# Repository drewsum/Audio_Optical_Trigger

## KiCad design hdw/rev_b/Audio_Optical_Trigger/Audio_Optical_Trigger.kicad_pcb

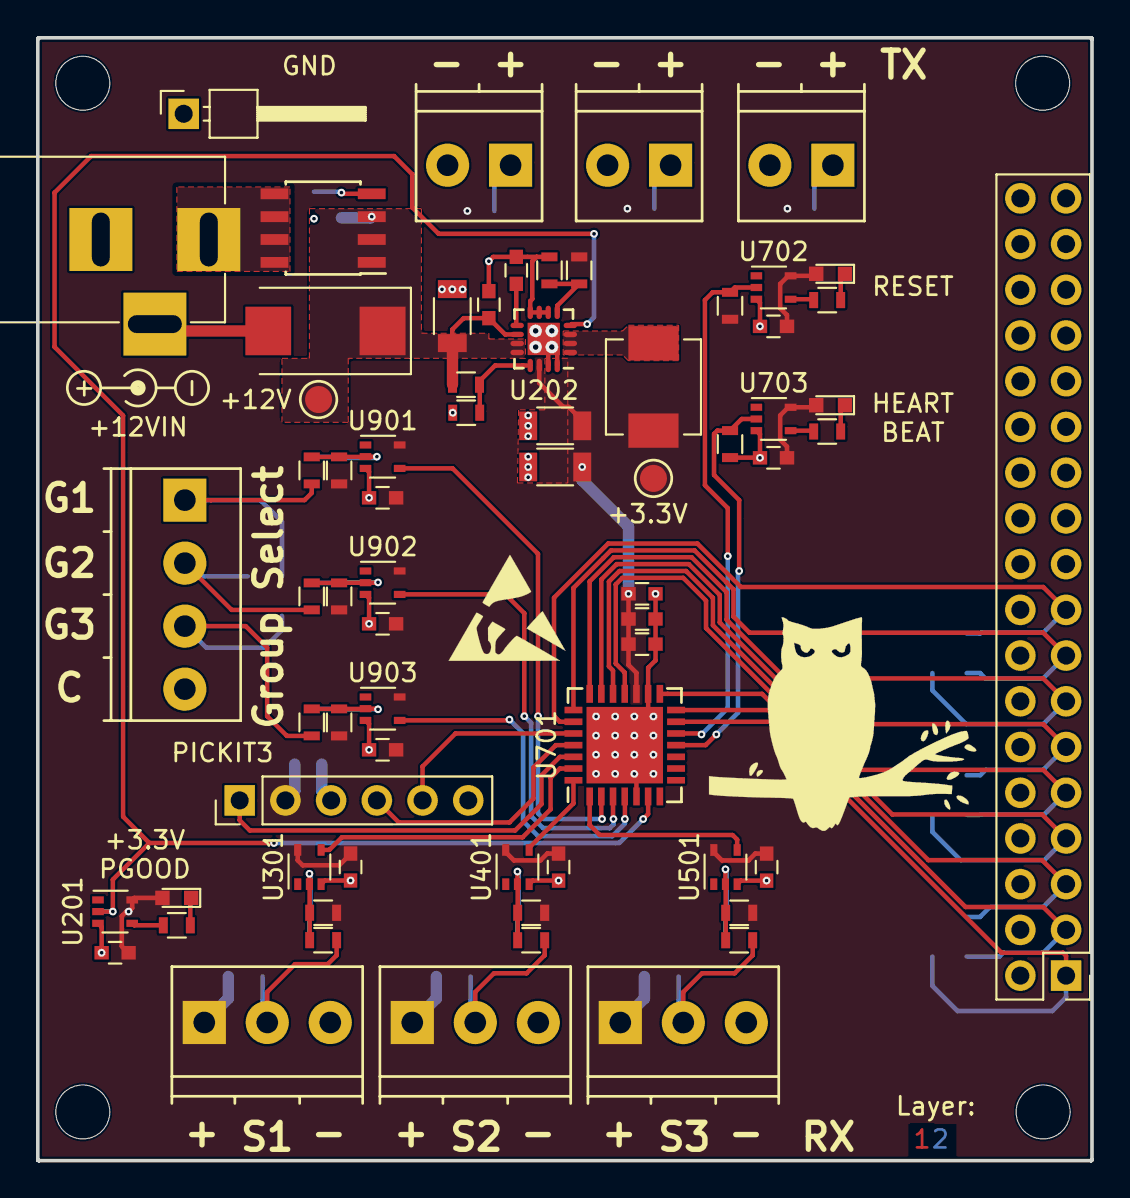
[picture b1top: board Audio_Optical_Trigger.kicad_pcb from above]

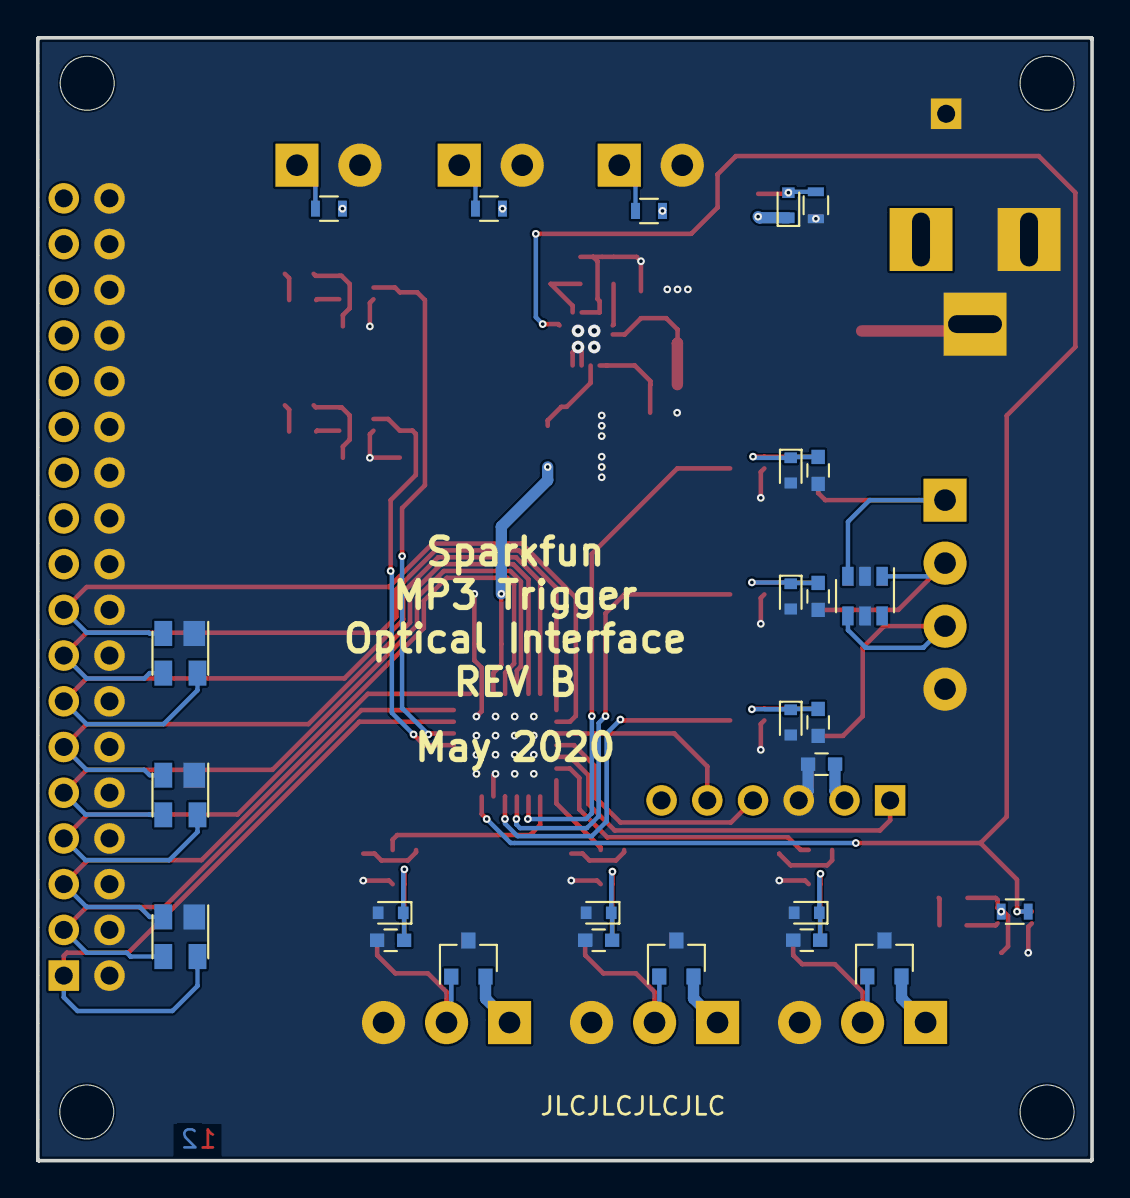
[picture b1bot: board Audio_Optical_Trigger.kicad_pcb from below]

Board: 2 copper layers, 58.6 x 62.4 mm, 98 parts (30 on the bottom side), 51 nets.

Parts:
C201, C205, C302, C402, C502, C601, C701, C704, C705, C904, C905, C906: 0.1uF; C_0603
C202: 100uF; CP_Tantalum_Case-D_EIA-7343-31_Reflow
C203: 10uF; C_1206
C204, C301, C401, C501, C702, C901, C902, C903: 10nF; C_0603
C206, C207: 22uF; C_1206
C703: 1nF; C_0603
D201: MM5Z10V; D_SOD-523
D202, D702: GREEN; LED_0603
D301, D401, D501: CM1213A-01SO; SOT-23
D302, D402, D502, D902, D903, D904: MM5Z3V6; D_SOD-523
D701: RED; LED_0603
D901: ESDA6V1BC6; SOT-23-6
D1001, D1002, D1003: SP0503BAHT; SOT-143
H1101, H1102, H1103, H1104: MountingHole; MountingHole_3mm
J201: +12VIN; BARREL_JACK
J301: TX1; TerminalBlock_Phoenix_PT-3.5mm_2pol
J302: RX1; TerminalBlock_Phoenix_PT-3.5mm_3pol
J401: TX2; TerminalBlock_Phoenix_PT-3.5mm_2pol
J402: RX2; TerminalBlock_Phoenix_PT-3.5mm_3pol
J501: TX3; TerminalBlock_Phoenix_PT-3.5mm_2pol
J502: RX3; TerminalBlock_Phoenix_PT-3.5mm_3pol
J601: PICKIT3; PinHeader_1x06_P2.54mm_Vertical
J901: Group Select; TerminalBlock_Phoenix_PT-3.5mm_4pol
J1001: Trigger Output; Pin_Header_Straight_2x18_Pitch2.54mm
L201: 2.2u; L_Vishay_IHLP-2020
Q201: IRF7404; SOIC-8_3.9x4.9mm_Pitch1.27mm
R201, R203, R303, R403, R503, R701, R702, R904, R905, R906: 10k; R_0603
R202, R207, R703, R704: 2k; R_0603
R204: 100k; R_0603
R205, R206: 10.5k; R_0603
R301, R401, R501: 0; R_0603
R302, R402, R502, R901, R902, R903: 100; R_0603
TP201: TP; Pin_Header_Angled_1x01_Pitch2.54mm
TP202, TP203: TP; Test_Point
U201, U702, U703, U901, U902, U903: 74LVC1G14; SOT-353_SC-70-5
U202: TPS62130; QFN-16-1EP_3x3mm_Pitch0.5mm
U301, U401, U501: 74LVC1G17; SOT-353_SC-70-5
U701: PIC18F27K40T-I_ML; QFN-28-1EP_6x6mm_Pitch0.65mm

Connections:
+3V3: C201.1, C206.1, C207.1, C302.1, C402.1, C502.1, C601.1, C701.1, C702.1, C703.1, C704.1, C705.1, C904.1, C905.1, C906.1, D202.2, D301.2, D401.2, D501.2, D701.2, D702.2, J302.1, J402.1, J502.1, J601.2, L201.2, R203.1, R206.1, R301.1, R303.1, R401.1, R403.1, R501.1, R503.1, R701.1, R904.1, R905.1, R906.1, TP203.1, U201.5, U202.14, U301.5, U401.5, U501.5, U701.17, U702.5, U703.5, U901.5, U902.5, U903.5
+12V: C202.1, C203.1, C205.1, D201.1, Q201.1, Q201.2, Q201.3, R204.1, TP202.1, U202.10, U202.11, U202.12
/Input Channel 1/YELLOW: D301.1, J302.2, R302.2
/Input Channel 2/YELLOW: D401.1, J402.2, R402.2
/Input Channel 3/YELLOW: D501.1, J502.2, R502.2
GND: C201.2, C202.2, C203.2, C204.2, C205.2, C206.2, C207.2, C301.2, C302.2, C401.2, C402.2, C501.2, C502.2, C601.2, C701.2, C702.2, C703.2, C704.2, C705.2, C901.2, C902.2, C903.2, C904.2, C905.2, C906.2, D301.3, D302.2, D401.3, D402.2, D501.3, D502.2, D901.2, D901.5, D902.2, D903.2, D904.2, D1001.1, D1002.1, D1003.1, J201.2, J201.3, J301.2, J302.3, J401.2, J402.3, J501.2, J502.3, J601.3, J901.4, J1001.2, J1001.4, J1001.6, J1001.8, J1001.10, J1001.12, J1001.14, J1001.16, J1001.18, J1001.20, J1001.22, J1001.24, J1001.26, J1001.28, J1001.30, J1001.32, J1001.34, J1001.36, R201.2, R205.2, R207.2, R702.2, TP201.1, U201.3, U202.6, U202.7, U202.8, U202.15, U202.16, U202.17, U301.3, U401.3, U501.3, U701.5, U701.16, U701.29, U702.3, U703.3, U901.3, U902.3, U903.3
Heartbeat_LED: R702.1, U701.11, U703.2
ICSPCLK: J601.5, U701.24
ICSPDAT: J601.4, U701.25
Input_Channel_1: U301.4, U701.27
Input_Channel_2: U401.4, U701.28
Input_Channel_3: U501.4, U701.1
unnamed: C204.1, U202.9
unnamed: C301.1, D302.1, R302.1, R303.2, U301.2
unnamed: C401.1, D402.1, R402.1, R403.2, U401.2
unnamed: C501.1, D502.1, R502.1, R503.2, U501.2
unnamed: C901.1, D902.1, R901.1, R904.2, U901.2
unnamed: C902.1, D903.1, R902.1, R905.2, U902.2
unnamed: C903.1, D904.1, R903.1, R906.2, U903.2
unnamed: D201.2, Q201.4, R201.1
unnamed: D202.1, R202.1
unnamed: D701.1, R703.1
unnamed: D702.1, R704.1
unnamed: D901.1, J901.2, R902.2
unnamed: D901.3, J901.1, R901.2
unnamed: D901.4, J901.3, R903.2
unnamed: J201.1, Q201.5, Q201.6, Q201.7, Q201.8
unnamed: J301.1, R301.2
unnamed: J401.1, R401.2
unnamed: J501.1, R501.2
unnamed: L201.1, U202.1, U202.2, U202.3
unnamed: R202.2, U201.4
unnamed: R204.2, R205.1, U202.13
unnamed: R206.2, R207.1, U202.5
unnamed: R703.2, U702.4
unnamed: R704.2, U703.4
Output_Group_Select_1: U701.2, U901.4
Output_Group_Select_2: U701.3, U902.4
Output_Group_Select_3: U701.4, U903.4
POS3P3_PGOOD: R203.2, U201.2, U202.4, U701.6
Reset_LED: R701.2, U701.12, U702.2
~MCLR: J601.1, U701.26
~Output_Group_1_Channel_1: D1001.4, J1001.1, U701.13
~Output_Group_1_Channel_2: D1001.3, J1001.3, U701.14
~Output_Group_1_Channel_3: D1001.2, J1001.5, U701.15
~Output_Group_2_Channel_1: D1002.4, J1001.7, U701.18
~Output_Group_2_Channel_2: D1002.3, J1001.9, U701.19
~Output_Group_2_Channel_3: D1002.2, J1001.11, U701.20
~Output_Group_3_Channel_1: D1003.4, J1001.13, U701.21
~Output_Group_3_Channel_2: D1003.3, J1001.15, U701.22
~Output_Group_3_Channel_3: D1003.2, J1001.17, U701.23

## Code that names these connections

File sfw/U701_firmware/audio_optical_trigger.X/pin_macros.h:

/* Microchip Technology Inc. and its subsidiaries.  You may use this software 
 * and any derivatives exclusively with Microchip products. 
 * 
 * THIS SOFTWARE IS SUPPLIED BY MICROCHIP "AS IS".  NO WARRANTIES, WHETHER 
 * EXPRESS, IMPLIED OR STATUTORY, APPLY TO THIS SOFTWARE, INCLUDING ANY IMPLIED 
 * WARRANTIES OF NON-INFRINGEMENT, MERCHANTABILITY, AND FITNESS FOR A 
 * PARTICULAR PURPOSE, OR ITS INTERACTION WITH MICROCHIP PRODUCTS, COMBINATION 
 * WITH ANY OTHER PRODUCTS, OR USE IN ANY APPLICATION. 
 *
 * IN NO EVENT WILL MICROCHIP BE LIABLE FOR ANY INDIRECT, SPECIAL, PUNITIVE, 
 * INCIDENTAL OR CONSEQUENTIAL LOSS, DAMAGE, COST OR EXPENSE OF ANY KIND 
 * WHATSOEVER RELATED TO THE SOFTWARE, HOWEVER CAUSED, EVEN IF MICROCHIP HAS 
 * BEEN ADVISED OF THE POSSIBILITY OR THE DAMAGES ARE FORESEEABLE.  TO THE 
 * FULLEST EXTENT ALLOWED BY LAW, MICROCHIP'S TOTAL LIABILITY ON ALL CLAIMS 
 * IN ANY WAY RELATED TO THIS SOFTWARE WILL NOT EXCEED THE AMOUNT OF FEES, IF 
 * ANY, THAT YOU HAVE PAID DIRECTLY TO MICROCHIP FOR THIS SOFTWARE.
 *
 * MICROCHIP PROVIDES THIS SOFTWARE CONDITIONALLY UPON YOUR ACCEPTANCE OF THESE 
 * TERMS. 
 */

/* 
 * File:   
 * Author: 
 * Comments:
 * Revision history: 
 */

// This is a guard condition so that contents of this file are not included
// more than once.  
#ifndef PIN_MACROS_H
#define	PIN_MACROS_H

#include <xc.h> // include processor files - each processor file is guarded.  

// PORT A
#define INPUT_CHANNEL_1_PIN                 PORTAbits.RA0
#define INPUT_CHANNEL_2_PIN                 PORTAbits.RA1
#define INPUT_CHANNEL_3_PIN                 PORTAbits.RA2
#define OUTPUT_GROUP_SELECT_1_PIN           PORTAbits.RA3
#define OUTPUT_GROUP_SELECT_2_PIN           PORTAbits.RA4
#define OUTPUT_GROUP_SELECT_3_PIN           PORTAbits.RA5
#define POS3P3_PGOOD_PIN                    PORTAbits.RA7

// PORT B
#define nOUTPUT_GROUP_2_CHANNEL_1_PIN       LATBbits.LATB0
#define nOUTPUT_GROUP_2_CHANNEL_2_PIN       LATBbits.LATB1
#define nOUTPUT_GROUP_2_CHANNEL_3_PIN       LATBbits.LATB2
#define nOUTPUT_GROUP_3_CHANNEL_1_PIN       LATBbits.LATB3
#define nOUTPUT_GROUP_3_CHANNEL_2_PIN       LATBbits.LATB4
#define nOUTPUT_GROUP_3_CHANNEL_3_PIN       LATBbits.LATB5

// PORT C
#define HEARTBEAT_LED_PIN                   LATCbits.LATC3
#define RESET_LED_PIN                       LATCbits.LATC4
#define nOUTPUT_GROUP_1_CHANNEL_1_PIN       LATCbits.LATC5
#define nOUTPUT_GROUP_1_CHANNEL_2_PIN       LATCbits.LATC6
#define nOUTPUT_GROUP_1_CHANNEL_3_PIN       LATCbits.LATC7

#endif	/* PIN_MACROS_H */

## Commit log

2019-01-10 Started messing around
2019-01-10 Removed unneeded output gate
2019-01-18 Basically finished schematic
2019-01-19 Reordered pages, added footprints
2019-01-19 Finished schematic
2019-01-19 Added BOM
2019-01-19 Revised BOM
2019-01-19 Pulled parts into PCB
2019-01-19 Fixed diode footprint issue
2019-01-19 Rewired a few nets, placed some parts
2019-01-19 Determined PCB shape
2019-01-20 Routed board in one go
2019-01-21 Adjusted routing, design rules
2020-05-01 Rev B schematic
2020-05-02 routed rev b board, created BOM, generated gerbers
2020-05-14 Added sfw project
2020-05-15 More sfw progress
2020-05-15 Simplified cod eto use blocking software delay debouncing
2020-05-19 Got sfw working without timers
2020-05-19 Got timer based implementation working
2020-05-19 extended trigger debounce period
2020-05-19 Few firmware tweaks
2020-05-19 fixed input edge detection
